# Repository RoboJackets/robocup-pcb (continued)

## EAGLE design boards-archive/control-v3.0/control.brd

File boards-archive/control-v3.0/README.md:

# Control Board

Board which contains micro-controller (MBED), power circuitry, FPGA, and all motor control circuitry.

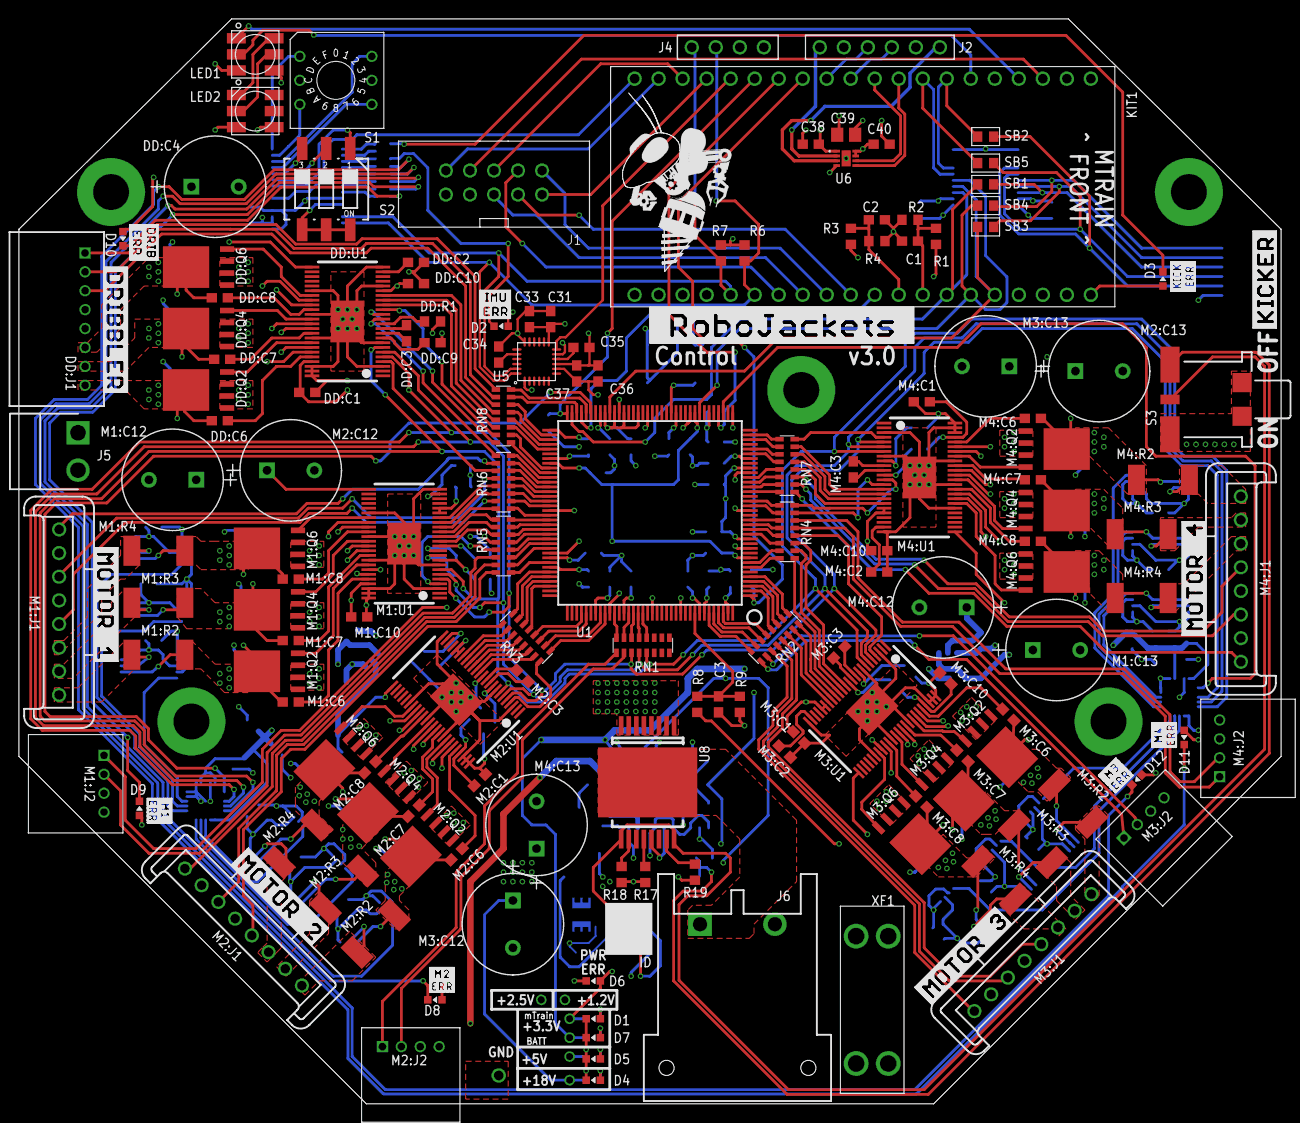
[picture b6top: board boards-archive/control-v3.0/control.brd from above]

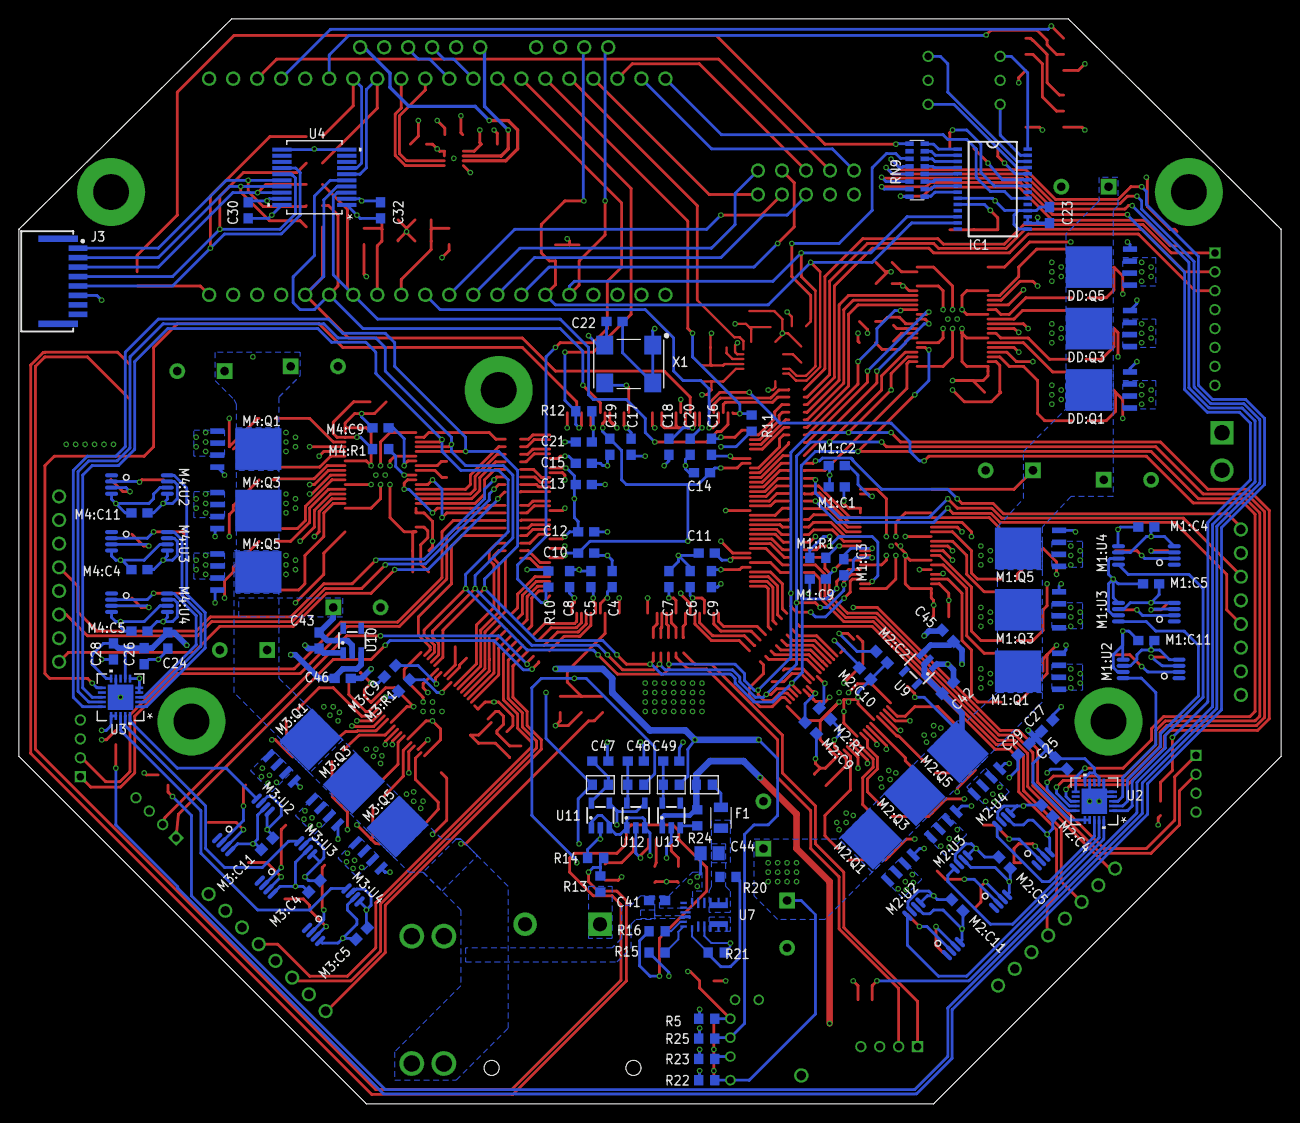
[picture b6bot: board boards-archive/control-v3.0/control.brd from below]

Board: 4 copper layers, 133.5 x 114.8 mm, 282 parts (121 on the bottom side), 327 nets.

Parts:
C1, C42, C43: 0.1uF 50V; C0603
C2, C3, C4, C5, C6, C7, C8, C9, C10, C11, C12, C13, C14, C15, C16, C17, C18, C19, C20, C21, C22, C23, C26, C27, C28, C29, C30, C32, C35, C38, C40: 0.1uF; C0603
C24, C25: 10uF; C0603
C31, C33, C37: 0.47uF; C0603
C34: 2200pF; C0603
C36: 10000pF; C0603
C39: 10uF; C0805
C41: GRM188R6YA106MA73D; C0603
C44: 22uF 16V; C0805
C45, C46, C47, C48, C49: 1uF; C0603
D1, D4, D5, D7: GREEN; CHIP-LED0603
D2, D3, D6, D8, D9, D10, D11, D12: RED; CHIP-LED0603
DD:C1, DD:C2: 1uF; C0603
DD:C3: 0.022uF 50V; C0603
DD:C4: ECA-1HHG221; CAP_PAN_10X12.5
DD:C6, DD:C7, DD:C8, DD:C10: 0.1uF 50V; C0603
DD:C9: 2.2uF 50V; C0603
DD:J1: 8-PIN_2MM-H; 2MM-8-H
DD:Q1, DD:Q2, DD:Q3, DD:Q4, DD:Q5, DD:Q6: IRFH7545; PQFN_5X6_E
DD:R1: 10k; R0603
DD:U1: DRV8303DCA; TSSOP-48_PAD
F1: 0805L200SLTHYR; FUSC2113X75
IC1: MCP23017-E/SS; SSOP-28
J1: SBH11-PBPC-D05-ST-BK; SBH11-*-D05-RA-VERT
J2: 6-PIN-HEADER
J3: HFW8R-1ST
J4: 4-PIN-HEADER
J5: B2PS-VH(LF)(SN); B2PS-CENTERED
J6: DF22-2; DF22-2-H
KIT1: MTRAIN; MTRAIN-KIT
LED1, LED2: APA102C-5050; APA102_5050
M1:C1, M1:C2, M2:C1, M2:C2, M3:C1, M3:C2, M4:C1, M4:C2: 1uF; C0603
M1:C3, M2:C3, M3:C3, M4:C3: 0.022uF 50V; C0603
M1:C4, M1:C5, M1:C11, M2:C4, M2:C5, M2:C11, M3:C4, M3:C5, M3:C11, M4:C4, M4:C5, M4:C11: 0.1uF; C0603
M1:C6, M1:C7, M1:C8, M1:C10, M2:C6, M2:C7, M2:C8, M2:C10, M3:C6, M3:C7, M3:C8, M3:C10, M4:C6, M4:C7, M4:C8, M4:C10: 0.1uF 50V; C0603
M1:C9, M2:C9, M3:C9, M4:C9: 2.2uF 50V; C0603
M1:C12, M1:C13, M2:C12, M2:C13, M3:C12, M3:C13, M4:C12, M4:C13: ECA-1HHG221; CAP_PAN_10X12.5
M1:J1, M2:J1, M3:J1, M4:J1: MKS-1658
M1:J2, M2:J2, M3:J2, M4:J2: 4-PIN_2MM-H; 2MM-4-H
M1:Q1, M1:Q2, M1:Q3, M1:Q4, M1:Q5, M1:Q6, M2:Q1, M2:Q2, M2:Q3, M2:Q4, M2:Q5, M2:Q6, M3:Q1, M3:Q2, M3:Q3, M3:Q4, M3:Q5, M3:Q6, M4:Q1, M4:Q2, M4:Q3, M4:Q4, M4:Q5, M4:Q6: IRFH7545; PQFN_5X6_E
M1:R1, M2:R1, M3:R1, M4:R1: 10k; R0603
M1:R2, M1:R3, M1:R4, M2:R2, M2:R3, M2:R4, M3:R2, M3:R3, M3:R4, M4:R2, M4:R3, M4:R4: 0.001 1%; R2512
M1:U1, M2:U1, M3:U1, M4:U1: DRV8303DCA; TSSOP-48_PAD
M1:U2, M1:U3, M1:U4, M2:U2, M2:U3, M2:U4, M3:U2, M3:U3, M3:U4, M4:U2, M4:U3, M4:U4: INA240PWR; PW0008A_N
R1, R8: 68k; R0603
R2, R3, R4, R9, R17, R24: 10k; R0603
R5, R11, R25: 330; R0603
R6, R7, R10, R12: 4.7k; R0603
R13: 270k; R0603
R14: 100k; R0603
R15: 43.2k; R0603
R16: 150k; R0603
R18, R19, R22, R23: 1k; R0603
R20: 160k 1%; R0603
R21: 30.1k 1%; R0603
RN1, RN2, RN3, RN4, RN5, RN6, RN7, RN8, RN9: 330; RA-8_2506
S1: 94HCB16T; HEX
S2: 219-03; CTS-219-03
S3: 34EWMSP12M6RT
SB1, SB2, SB3, SB4, SB5, SB6, SB7, SB8, SB9: SOLDERBRIDGESB0603; SB0603
U1: XC3S250E-4TQG144C; TQFP144
U2, U3: ADS8028IRTJT; RTJ20_2P7X2P7
U4: ADUM3151ARSZ; RS_20
U5: MPU-6050; QFN-24-4MM2
U6: DRV8837X; DSG_8
U7: MPM3620GQV-P
U8: VND5E006ASPTR-E; POWERSO-16
U9, U10: TLV70450; SOT-23-5
U11: MCP1824T-1202E/OT; SOT-23-5
U12: MCP1824T-2502E/OT; SOT-23-5
U13: TLV70233DBVR; SOT-23-5
U$1: ERR-DRIB
U$2: ROBOJACKETS
U$3: MOTOR-1
U$4: DRIBBLER
U$5: MOTOR-2
U$6: MOTOR-3
U$7: MOTOR-4
U$8: ERR-M1
U$9: KICKER
U$10: ERR-IMU
U$11: ROBOBUZZ_1.0X2
U$12: ERR-M2
U$13: ERR-M3
U$14: ERR-M4
U$15: ERR-KICK
X1: ASV-18.432MHZ-EJ-T; ASV
XF1: 30A; 3557-2

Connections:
3.3V-EN: R24.1, U13.3
3V3-LED: D7.A, R25.1
5V-LED: D5.A, R23.2
18.5V-LED: D4.A, R22.1
!CS!-ADC1: U1.67, U2.11
!CS!-ADC2: U1.39, U3.11
!CS!-FPGA: KIT1.P$31, U1.69
!CS!-KICK: KIT1.P$8, SB5.1, U4.6
!CS!-RAD0: J1.10, KIT1.P$17
!CS!-RAD1: J1.4, KIT1.P$3
!RST!-KICK: KIT1.P$7, SB2.1, U4.7
!RST!-RADIO: J1.5, KIT1.P$19
!SCS!-KICK: J3.4, SB5.2, U4.15
!SRST!-KICK: J3.5, SB2.2, U4.14
+1.2V: C6.1, C10.1, C14.1, C19.1, SB7.2, U1.9, U1.45, U1.80, U1.115
+1.2V-PRE: C47.1, SB7.1, U11.5
+2.5V: C4.1, C9.1, C15.1, C20.1, R10.2, R11.2, SB8.2, U1.30, U1.65, U1.102, U1.137
+2.5V-PRE: C48.1, SB8.1, U12.5
+3.3V: C5.1, C7.1, C8.1, C11.1, C12.1, C13.1, C16.1, C17.1, C18.1, C21.1, C22.1, C23.1, C30.1, C31.1, C32.1, C33.1, C36.1, C37.1, C40.1, D2.A, D3.A, D6.A, D8.A, D9.A, D10.A, D11.A, D12.A, IC1.9, IC1.15, IC1.18, J2.2, J4.2, KIT1.VDD, R5.1, R6.2, R7.2, R12.1, U1.13, U1.28, U1.42, U1.49, U1.57, U1.60, U1.62, U1.64, U1.79, U1.100, U1.121, U1.138, U1.143, U4.1, U4.20, U5.8, U5.13, U6.7, U6.8, U11.1, U11.3, U12.1, U12.3, X1.1, X1.4
+3V3: DD:C1.1, DD:C10.1, DD:R1.1, DD:U1.19, DD:U1.45, M1:C1.1, M1:C10.1, M1:R1.1, M1:U1.19, M1:U1.20, M1:U1.45, M2:C1.1, M2:C10.1, M2:R1.1, M2:U1.19, M2:U1.20, M2:U1.45, M3:C1.1, M3:C10.1, M3:R1.1, M3:U1.19, M3:U1.20, M3:U1.45, M4:C1.1, M4:C10.1, M4:R1.1, M4:U1.19, M4:U1.20, M4:U1.45, R25.2, SB9.2
+3V3-PRE: C49.1, SB9.1, U13.5
+5V: C38.1, C39.1, DD:J1.5, J1.6, KIT1.VIN, LED1.1, LED2.1, M1:C4.1, M1:C5.1, M1:C11.1, M1:J1.4, M1:J2.4, M1:U2.5, M1:U2.7, M1:U3.5, M1:U3.7, M1:U4.5, M1:U4.7, M2:C4.1, M2:C5.1, M2:C11.1, M2:J1.4, M2:J2.4, M2:U2.5, M2:U2.7, M2:U3.5, M2:U3.7, M2:U4.5, M2:U4.7, M3:C4.1, M3:C5.1, M3:C11.1, M3:J1.4, M3:J2.4, M3:U2.5, M3:U2.7, M3:U3.5, M3:U3.7, M3:U4.5, M3:U4.7, M4:C4.1, M4:C5.1, M4:C11.1, M4:J1.4, M4:J2.4, M4:U2.5, M4:U2.7, M4:U3.5, M4:U3.7, M4:U4.5, M4:U4.7, R3.1, R23.1, R24.2, SB6.2, U6.1, U13.1
+5V-FUSE: C44.1, F1.1, R20.2, U7.789
+5V-PRE2: F1.2, SB6.1
+18.5V: C41.1, C42.1, C43.1, DD:C4.1, DD:Q1.5678, DD:Q3.5678, DD:Q5.5678, DD:U1.25, M1:C12.1, M1:C13.1, M1:Q1.5678, M1:Q3.5678, M1:Q5.5678, M1:U1.25, M2:C12.1, M2:C13.1, M2:Q1.5678, M2:Q3.5678, M2:Q5.5678, M2:U1.25, M3:C12.1, M3:C13.1, M3:Q1.5678, M3:Q3.5678, M3:Q5.5678, M3:U1.25, M4:C12.1, M4:C13.1, M4:Q1.5678, M4:Q3.5678, M4:Q5.5678, M4:U1.25, R1.1, R8.1, R22.2, U7.16, U9.2, U10.2, XF1.3, XF1.4
AAM: R15.2, U7.18
ADC1-5V: C25.1, C27.1, C29.1, C45.1, U2.7, U2.10, U2.16, U2.17, U9.3
ADC2-5V: C24.1, C26.1, C28.1, C46.1, U3.7, U3.10, U3.16, U3.17, U10.3
BATT-FPGA: C3.1, R8.2, R9.1, U1.136
CPOUT: C34.1, U5.20
CS1: R18.2, U8.10
CS2: R19.2, U8.15
CS-DIS: R17.2, U8.12
DD-!CS: DD:U1.4, RN6.11
DD-A-H: DD:U1.13, RN6.9
DD-A-L: DD:U1.14, RN8.16
DD-B-H: DD:U1.15, RN8.15
DD-B-L: DD:U1.16, RN8.14
DD-C-H: DD:U1.17, RN8.13
DD-C-L: DD:U1.18, RN8.12
DD-H1: DD:J1.3, RN8.11
DD-H2: DD:J1.2, RN8.10
DD-H3: DD:J1.1, RN8.9
DD:AVDD: DD:C2.1, DD:U1.23
DD:BST-A: DD:C6.1, DD:U1.44
DD:BST-B: DD:C7.1, DD:U1.39
DD:BST-C: DD:C8.1, DD:U1.34
DD:CP1: DD:C3.1, DD:U1.10
DD:CP2: DD:C3.2, DD:U1.11
DD:EN-GATE: DD:R1.2, DD:U1.12
DD:GH-A: DD:Q1.4, DD:U1.43
DD:GH-B: DD:Q3.4, DD:U1.38
DD:GH-C: DD:Q5.4, DD:U1.33
DD:GL-A: DD:Q2.4, DD:U1.41
DD:GL-B: DD:Q4.4, DD:U1.36
DD:GL-C: DD:Q6.4, DD:U1.31
DD:GVDD: DD:C9.1, DD:U1.9
DD:PHASE-A: DD:C6.2, DD:J1.8, DD:Q1.1, DD:Q1.2, DD:Q1.3, DD:Q2.5678, DD:U1.42
DD:PHASE-B: DD:C7.2, DD:J1.7, DD:Q3.1, DD:Q3.2, DD:Q3.3, DD:Q4.5678, DD:U1.37
DD:PHASE-C: DD:C8.2, DD:J1.6, DD:Q5.1, DD:Q5.2, DD:Q5.3, DD:Q6.5678, DD:U1.32
DIP-1: IC1.22, S2.1
DIP-2: IC1.23, S2.2
DIP-3: IC1.24, S2.3
DOT-CLK: KIT1.P$6, LED1.5
DOT-CLK-INTER: LED1.2, LED2.5
DOT-DATA: KIT1.P$4, LED1.4
DOT-DATA-INTER: LED1.3, LED2.4
EN: R16.2, U7.17
EN-PWR: R16.1, S3.2, U8.9, U8.16
EN-PWR-PRE: R13.1, R14.2, S3.1
FB: R20.1, R21.2, U7.1
FPGA-CLK: U1.50, X1.3
FPGA-DONE: KIT1.P$15, R11.1, U1.72
FPGA-INIT: KIT1.P$14, R12.2, U1.40
FPGA-PROG: KIT1.P$13, R10.1, U1.1
GND: C1.2, C2.2, C3.2, C4.2, C5.2, C6.2, C7.2, C8.2, C9.2, C10.2, C11.2, C12.2, C13.2, C14.2, C15.2, C16.2, C17.2, C18.2, C19.2, C20.2, C21.2, C22.2, C23.2, C24.2, C25.2, C26.2, C27.2, C28.2, C29.2, C30.2, C31.2, C32.2, C33.2, C34.2, C35.2, C36.2, C37.2, C38.2, C39.2, C40.2, C41.2, C42.2, C43.2, C44.2, C45.2, C46.2, C47.2, C48.2, C49.2, D1.C, D4.C, D5.C, D7.C, DD:C1.2, DD:C2.2, DD:C4.2, DD:C9.2, DD:C10.2, DD:J1.4, DD:Q2.1, DD:Q2.2, DD:Q2.3, DD:Q4.1, DD:Q4.2, DD:Q4.3, DD:Q6.1, DD:Q6.2, DD:Q6.3, DD:U1.3, DD:U1.8, DD:U1.20, DD:U1.24, DD:U1.30, DD:U1.35, DD:U1.40, DD:U1.46, DD:U1.47, DD:U1.48, DD:U1.PAD, IC1.10, IC1.16, IC1.17, J1.7, J2.5, J3.6, J4.1, J5.2, J6.2, KIT1.GND, LED1.6, LED2.6, M1:C1.2, M1:C2.2, M1:C4.2, M1:C5.2, M1:C9.2, M1:C10.2, M1:C11.2, M1:C12.2, M1:C13.2, M1:J1.2, M1:J2.3, M1:Q2.1, M1:Q2.2, M1:Q2.3, M1:Q4.1, M1:Q4.2, M1:Q4.3, M1:Q6.1, M1:Q6.2, M1:Q6.3, M1:U1.3, M1:U1.8, M1:U1.24, M1:U1.30, M1:U1.35, M1:U1.40, M1:U1.46, M1:U1.47, M1:U1.48, M1:U1.PAD, M1:U2.4, M1:U2.6, M1:U3.4, M1:U3.6, M1:U4.4, M1:U4.6, M2:C1.2, M2:C2.2, M2:C4.2, M2:C5.2, M2:C9.2, M2:C10.2, M2:C11.2, M2:C12.2, M2:C13.2, M2:J1.2, M2:J2.3, M2:Q2.1, M2:Q2.2, M2:Q2.3, M2:Q4.1, M2:Q4.2, M2:Q4.3, M2:Q6.1, M2:Q6.2, M2:Q6.3, M2:U1.3, M2:U1.8, M2:U1.24, M2:U1.30, M2:U1.35, M2:U1.40, M2:U1.46, M2:U1.47, M2:U1.48, M2:U1.PAD, M2:U2.4, M2:U2.6, M2:U3.4, M2:U3.6, M2:U4.4, M2:U4.6, M3:C1.2, M3:C2.2, M3:C4.2, M3:C5.2, M3:C9.2, M3:C10.2, M3:C11.2, M3:C12.2, M3:C13.2, M3:J1.2, M3:J2.3, M3:Q2.1, M3:Q2.2, M3:Q2.3, M3:Q4.1, M3:Q4.2, M3:Q4.3, M3:Q6.1, M3:Q6.2, M3:Q6.3, M3:U1.3, M3:U1.8, M3:U1.24, M3:U1.30, M3:U1.35, M3:U1.40, M3:U1.46, M3:U1.47, M3:U1.48, M3:U1.PAD, M3:U2.4, M3:U2.6, M3:U3.4, M3:U3.6, M3:U4.4, M3:U4.6, M4:C1.2, M4:C2.2, M4:C4.2, M4:C5.2, M4:C9.2, M4:C10.2, M4:C11.2, M4:C12.2, M4:C13.2, M4:J1.2, M4:J2.3, M4:Q2.1, M4:Q2.2, M4:Q2.3, M4:Q4.1, M4:Q4.2, M4:Q4.3, M4:Q6.1, M4:Q6.2, M4:Q6.3, M4:U1.3, M4:U1.8, M4:U1.24, M4:U1.30, M4:U1.35, M4:U1.40, M4:U1.46, M4:U1.47, M4:U1.48, M4:U1.PAD, M4:U2.4, M4:U2.6, M4:U3.4, M4:U3.6, M4:U4.4, M4:U4.6, R2.2, R4.2, R9.2, R14.1, R15.1, R17.1, R18.1, R19.1, R21.1, S1.C1, S1.C2, S2.4, S2.5, S2.6, S3.3, S3.LEG1, S3.LEG3, U1.11, U1.19, U1.27, U1.37, U1.46, U1.55, U1.61, U1.73, U1.90, U1.99, U1.118, U1.127, U1.133, U2.4, U2.5, U2.6, U2.9, U2.21, U3.4, U3.5, U3.6, U3.9, U3.21, U4.2, U4.10, U4.11, U4.19, U5.1, U5.9, U5.11, U5.18, U6.4, U6.9, U7.3, U7.12, U7.13, U7.14, U8.13, U9.1, U10.1, U11.2, U12.2, U13.2, X1.2
GPB0: IC1.1, RN9.8
GPB1: IC1.2, RN9.7
GPB2: IC1.3, RN9.6
GPB3: IC1.4, RN9.5
GPB4: IC1.5, RN9.4
GPB5: IC1.6, RN9.3
GPB6: IC1.7, RN9.2
GPB7: IC1.8, RN9.1
HEX-0: IC1.28, S1.1
HEX-1: IC1.25, S1.2
HEX-2: IC1.27, S1.4
HEX-3: IC1.26, S1.8
INT-IO: IC1.20, KIT1.P$20
INT-MPU: KIT1.P$16, U5.12
INT-RAD0: J1.9, KIT1.P$30
INT-RAD1: J1.3, KIT1.P$18
LED-DD: D10.C, RN9.16
LED-KICK: D3.C, RN9.9
LED-M1: D9.C, RN9.15
LED-M2: D8.C, RN9.14
LED-M3: D12.C, RN9.13
LED-M4: D11.C, RN9.12
LED-MPU: D2.C, RN9.11
M1-!CS: M1:U1.4, RN5.13
M1-A-H: M1:U1.15, RN5.9
M1-A-L: M1:U1.16, RN6.16
M1-B-H: M1:U1.13, RN5.11
M1-B-L: M1:U1.14, RN5.10
M1-C-H: M1:U1.17, RN6.14
M1-C-L: M1:U1.18, RN6.13
M1-ENC-A: M1:J2.2, RN5.14
M1-ENC-B: M1:J2.1, RN5.12
M1-H1: M1:J1.1, RN6.10
M1-H2: M1:J1.3, RN6.12
M1-H3: M1:J1.5, RN6.15
M1-SENSE-A: M1:U3.8, U2.2
M1-SENSE-B: M1:U2.8, U2.3
M1-SENSE-C: M1:U4.8, U2.1
M1:AIN+: M1:C7.2, M1:Q3.1, M1:Q3.2, M1:Q3.3, M1:Q4.5678, M1:R3.1, M1:U1.37, M1:U3.2
M1:AVDD: M1:C2.1, M1:U1.23
M1:BIN+: M1:C6.2, M1:Q1.1, M1:Q1.2, M1:Q1.3, M1:Q2.5678, M1:R2.1, M1:U1.42, M1:U2.2
M1:BST-A: M1:C6.1, M1:U1.44
M1:BST-B: M1:C7.1, M1:U1.39
M1:BST-C: M1:C8.1, M1:U1.34
M1:CIN+: M1:C8.2, M1:Q5.1, M1:Q5.2, M1:Q5.3, M1:Q6.5678, M1:R4.1, M1:U1.32, M1:U4.2
M1:CP1: M1:C3.1, M1:U1.10
M1:CP2: M1:C3.2, M1:U1.11
M1:EN-GATE: M1:R1.2, M1:U1.12
M1:GH-A: M1:Q1.4, M1:U1.43
M1:GH-B: M1:Q3.4, M1:U1.38
M1:GH-C: M1:Q5.4, M1:U1.33
M1:GL-A: M1:Q2.4, M1:U1.41
M1:GL-B: M1:Q4.4, M1:U1.36
M1:GL-C: M1:Q6.4, M1:U1.31
M1:GVDD: M1:C9.1, M1:U1.9
M1:PHASE-A: M1:J1.7, M1:R3.2, M1:U3.3
M1:PHASE-B: M1:J1.8, M1:R2.2, M1:U2.3
M1:PHASE-C: M1:J1.6, M1:R4.2, M1:U4.3
M2-!CS: M2:U1.4, RN3.16
M2-A-H: M2:U1.15, RN3.13
M2-A-L: M2:U1.16, RN3.12
M2-B-H: M2:U1.13, RN3.15
M2-B-L: M2:U1.14, RN3.14
M2-C-H: M2:U1.17, RN3.11
M2-C-L: M2:U1.18, RN3.10
M2-ENC-A: M2:J2.2, RN1.10
M2-ENC-B: M2:J2.1, RN1.9
M2-H1: M2:J1.1, RN5.15
M2-H2: M2:J1.3, RN5.16
M2-H3: M2:J1.5, RN3.9
M2-SENSE-A: M2:U3.8, U2.19
M2-SENSE-B: M2:U2.8, U2.20
M2-SENSE-C: M2:U4.8, U2.18
M2:AIN+: M2:C7.2, M2:Q3.1, M2:Q3.2, M2:Q3.3, M2:Q4.5678, M2:R3.1, M2:U1.37, M2:U3.2
M2:AVDD: M2:C2.1, M2:U1.23
M2:BIN+: M2:C6.2, M2:Q1.1, M2:Q1.2, M2:Q1.3, M2:Q2.5678, M2:R2.1, M2:U1.42, M2:U2.2
M2:BST-A: M2:C6.1, M2:U1.44
M2:BST-B: M2:C7.1, M2:U1.39
M2:BST-C: M2:C8.1, M2:U1.34
M2:CIN+: M2:C8.2, M2:Q5.1, M2:Q5.2, M2:Q5.3, M2:Q6.5678, M2:R4.1, M2:U1.32, M2:U4.2
M2:CP1: M2:C3.1, M2:U1.10
M2:CP2: M2:C3.2, M2:U1.11
M2:EN-GATE: M2:R1.2, M2:U1.12
M2:GH-A: M2:Q1.4, M2:U1.43
M2:GH-B: M2:Q3.4, M2:U1.38
M2:GH-C: M2:Q5.4, M2:U1.33
M2:GL-A: M2:Q2.4, M2:U1.41
M2:GL-B: M2:Q4.4, M2:U1.36
M2:GL-C: M2:Q6.4, M2:U1.31
M2:GVDD: M2:C9.1, M2:U1.9
M2:PHASE-A: M2:J1.7, M2:R3.2, M2:U3.3
M2:PHASE-B: M2:J1.8, M2:R2.2, M2:U2.3
M2:PHASE-C: M2:J1.6, M2:R4.2, M2:U4.3
M3-!CS: M3:U1.4, RN4.12
M3-A-H: M3:U1.15, RN4.9
M3-A-L: M3:U1.16, RN2.16
M3-B-H: M3:U1.13, RN4.11
M3-B-L: M3:U1.14, RN4.10
M3-C-H: M3:U1.17, RN2.15
M3-C-L: M3:U1.18, RN2.14
M3-ENC-A: M3:J2.2, RN2.10
M3-ENC-B: M3:J2.1, RN2.9
M3-H1: M3:J1.1, RN2.11
M3-H2: M3:J1.3, RN2.12
M3-H3: M3:J1.5, RN2.13
M3-SENSE-A: M3:U3.8, U3.19
M3-SENSE-B: M3:U2.8, U3.20
M3-SENSE-C: M3:U4.8, U3.18
M3:AIN+: M3:C7.2, M3:Q3.1, M3:Q3.2, M3:Q3.3, M3:Q4.5678, M3:R3.1, M3:U1.37, M3:U3.2
M3:AVDD: M3:C2.1, M3:U1.23
M3:BIN+: M3:C6.2, M3:Q1.1, M3:Q1.2, M3:Q1.3, M3:Q2.5678, M3:R2.1, M3:U1.42, M3:U2.2
M3:BST-A: M3:C6.1, M3:U1.44
M3:BST-B: M3:C7.1, M3:U1.39
M3:BST-C: M3:C8.1, M3:U1.34
M3:CIN+: M3:C8.2, M3:Q5.1, M3:Q5.2, M3:Q5.3, M3:Q6.5678, M3:R4.1, M3:U1.32, M3:U4.2
M3:CP1: M3:C3.1, M3:U1.10
M3:CP2: M3:C3.2, M3:U1.11
M3:EN-GATE: M3:R1.2, M3:U1.12
M3:GH-A: M3:Q1.4, M3:U1.43
M3:GH-B: M3:Q3.4, M3:U1.38
M3:GH-C: M3:Q5.4, M3:U1.33
M3:GL-A: M3:Q2.4, M3:U1.41
M3:GL-B: M3:Q4.4, M3:U1.36
M3:GL-C: M3:Q6.4, M3:U1.31
M3:GVDD: M3:C9.1, M3:U1.9
M3:PHASE-A: M3:J1.7, M3:R3.2, M3:U3.3
M3:PHASE-B: M3:J1.8, M3:R2.2, M3:U2.3
M3:PHASE-C: M3:J1.6, M3:R4.2, M3:U4.3
M4-!CS: M4:U1.4, RN7.16
M4-A-H: M4:U1.15, RN7.15
M4-A-L: M4:U1.16, RN7.14
M4-B-H: M4:U1.13, RN4.16
M4-B-L: M4:U1.14, RN4.15
M4-C-H: M4:U1.17, RN7.13
M4-C-L: M4:U1.18, RN7.12
M4-ENC-A: M4:J2.2, RN4.14
M4-ENC-B: M4:J2.1, RN4.13
M4-H1: M4:J1.1, RN7.9
M4-H2: M4:J1.3, RN7.10
M4-H3: M4:J1.5, RN7.11
M4-SENSE-A: M4:U3.8, U3.2
M4-SENSE-B: M4:U2.8, U3.1
M4-SENSE-C: M4:U4.8, U3.3
M4:AIN+: M4:C7.2, M4:Q3.1, M4:Q3.2, M4:Q3.3, M4:Q4.5678, M4:R3.1, M4:U1.37, M4:U3.2
M4:AVDD: M4:C2.1, M4:U1.23
M4:BIN+: M4:C6.2, M4:Q1.1, M4:Q1.2, M4:Q1.3, M4:Q2.5678, M4:R2.1, M4:U1.42, M4:U2.2
M4:BST-A: M4:C6.1, M4:U1.44
M4:BST-B: M4:C7.1, M4:U1.39
M4:BST-C: M4:C8.1, M4:U1.34
M4:CIN+: M4:C8.2, M4:Q5.1, M4:Q5.2, M4:Q5.3, M4:Q6.5678, M4:R4.1, M4:U1.32, M4:U4.2
M4:CP1: M4:C3.1, M4:U1.10
M4:CP2: M4:C3.2, M4:U1.11
M4:EN-GATE: M4:R1.2, M4:U1.12
M4:GH-A: M4:Q1.4, M4:U1.43
M4:GH-B: M4:Q3.4, M4:U1.38
M4:GH-C: M4:Q5.4, M4:U1.33
M4:GL-A: M4:Q2.4, M4:U1.41
M4:GL-B: M4:Q4.4, M4:U1.36
M4:GL-C: M4:Q6.4, M4:U1.31
M4:GVDD: M4:C9.1, M4:U1.9
M4:PHASE-A: M4:J1.7, M4:R3.2, M4:U3.3
M4:PHASE-B: M4:J1.8, M4:R2.2, M4:U2.3
M4:PHASE-C: M4:J1.6, M4:R4.2, M4:U4.3
MISO: KIT1.P$35, SB4.1, U1.44, U4.5
MISO-AUX: DD:U1.6, M1:U1.6, M2:U1.6, M3:U1.6, M4:U1.6, RN1.12, U2.14, U3.14
MISO-KICK: J3.1, SB4.2, U4.16
MISO-RADIO: J1.8, KIT1.P$28
MK-ENC-A: J2.3, KIT1.P$12
MK-ENC-B: J2.4, KIT1.P$11
MK-IN1: KIT1.P$10, U6.6
MK-IN2: KIT1.P$9, U6.5
MK-OUT1: J2.1, U6.2
MK-OUT2: J2.6, U6.3
MOSI: KIT1.P$36, SB3.1, U1.63, U4.4
MOSI-AUX: DD:U1.5, M1:U1.5, M2:U1.5, M3:U1.5, M4:U1.5, RN1.11, U2.13, U3.13
MOSI-KICK: J3.2, SB3.2, U4.17
MOSI-RADIO: J1.2, KIT1.P$27
PWR-ERR: D6.C, U11.4, U12.4
R-P1: RN8.1, U1.82
R-P2: RN8.2, U1.81
R-P3: RN8.3, U1.77
R-P4: RN8.4, U1.76
R-P5: RN8.5, U1.75
R-P6: RN8.6, U1.74
R-P7: RN8.7, U1.70
R-P8: RN8.8, U1.68
R-P9: RN6.1, U1.91
R-P10: RN6.2, U1.89
R-P11: RN6.3, U1.88
R-P12: RN6.4, U1.87
R-P13: RN6.5, U1.86
R-P14: RN6.6, U1.85
R-P15: RN6.7, U1.84
R-P16: RN6.8, U1.83
R-P17: RN5.1, U1.101
R-P18: RN5.2, U1.98
R-P19: RN5.3, U1.97
R-P20: RN5.4, U1.96
R-P21: RN5.5, U1.95
R-P22: RN5.6, U1.94
R-P23: RN5.7, U1.93
R-P24: RN5.8, U1.92
R-P25: RN3.1, U1.117
R-P26: RN3.2, U1.116
R-P27: RN3.3, U1.113
R-P28: RN3.4, U1.112
R-P29: RN3.5, U1.106
R-P30: RN3.6, U1.105
R-P31: RN3.7, U1.104
R-P32: RN3.8, U1.103
R-P36: RN1.4, U1.125
R-P37: RN1.5, U1.124
R-P38: RN1.6, U1.123
R-P39: RN1.7, U1.122
R-P40: RN1.8, U1.119
R-P41: RN2.1, U1.5
R-P42: RN2.2, U1.4
R-P43: RN2.3, U1.3
R-P44: RN2.4, U1.2
R-P45: RN2.5, U1.142
R-P46: RN2.6, U1.141
R-P47: RN2.7, U1.140
R-P48: RN2.8, U1.139
R-P49: RN4.1, U1.21
R-P50: RN4.2, U1.20
R-P51: RN4.3, U1.17
R-P52: RN4.4, U1.16
R-P53: RN4.5, U1.15
R-P54: RN4.6, U1.14
R-P55: RN4.7, U1.8
R-P56: RN4.8, U1.7
R-P57: RN7.1, U1.35
R-P58: RN7.2, U1.34
R-P59: RN7.3, U1.32
R-P60: RN7.4, U1.31
R-P61: RN7.5, U1.26
R-P62: RN7.6, U1.25
R-P63: RN7.7, U1.24
R-P64: RN7.8, U1.23
REGOUT: C35.1, U5.10
SCK: KIT1.P$34, SB1.1, U1.71, U4.3
SCK-AUX: DD:U1.7, M1:U1.7, M2:U1.7, M3:U1.7, M4:U1.7, RN1.13, U2.15, U3.15
SCK-KICK: J3.3, SB1.2, U4.18
SCK-RADIO: J1.1, KIT1.P$29
SCL: IC1.12, J4.4, KIT1.P$25, R7.1, U5.23
SDA: IC1.13, J4.3, KIT1.P$26, R6.1, U5.24
SENSE-BATT: C1.1, KIT1.P$33, R1.2, R2.1
SENSE-VIN: C2.1, KIT1.P$32, R3.2, R4.1
VBATT: J5.1, U8.1, U8.2, U8.3, U8.4, U8.5, U8.6, U8.7, U8.8, XF1.1, XF1.2
VDD-LED: D1.A, R5.2
VIN: J6.1, R13.2, U8.17
